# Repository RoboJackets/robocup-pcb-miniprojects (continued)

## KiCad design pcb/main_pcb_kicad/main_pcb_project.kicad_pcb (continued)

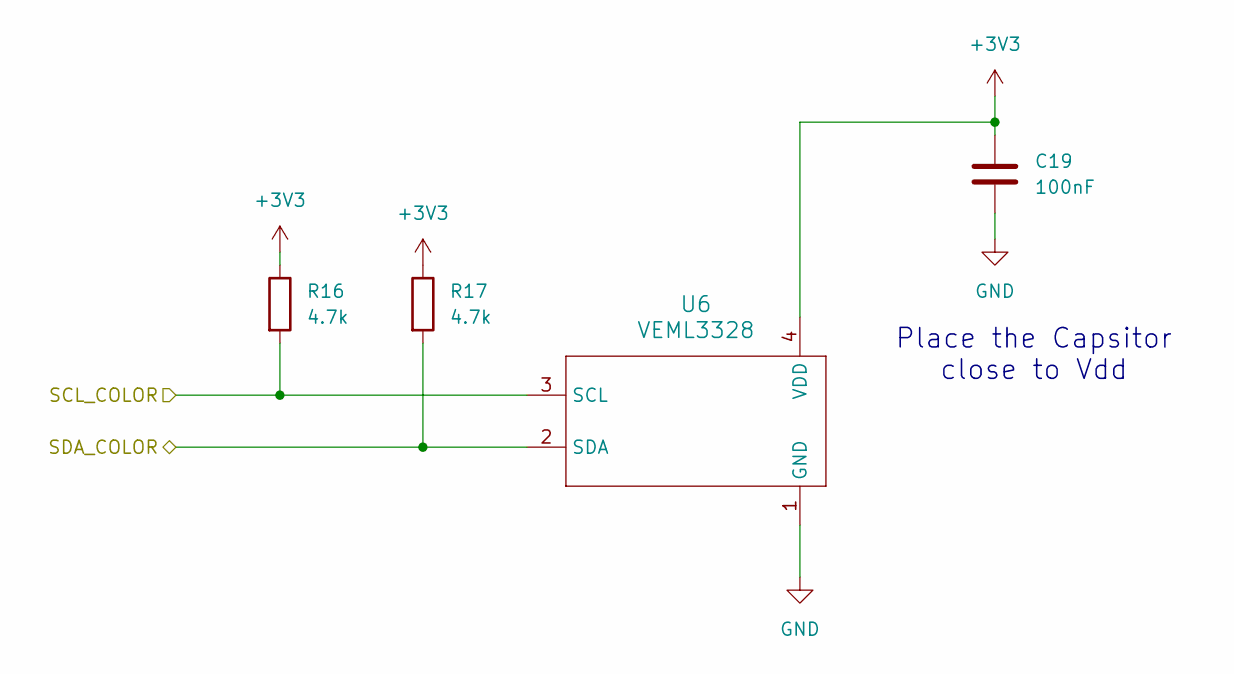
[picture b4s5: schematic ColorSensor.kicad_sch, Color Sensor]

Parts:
C19: 100nF; C_0603_1608Metric; Manufacturer P/N CC0603KRX7R9BB104
R16, R17: 4.7k; R_0402_1005Metric; Manufacturer P/N RC0402FR-074K7L
U6: VEML3328; SMD_L3328_VIS; Manufacturer P/N VEML3328

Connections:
+3V3: C19.1, R16.1, R17.1, U6.4 (VDD); also elsewhere on the board
/SCL_COLOR: R16.2, U6.3 (SCL); also elsewhere on the board
/SDA_COLOR: R17.2, U6.2 (SDA); also elsewhere on the board
GND: C19.2, U6.1 (GND); also elsewhere on the board

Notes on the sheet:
Place the Capsitor close to Vdd

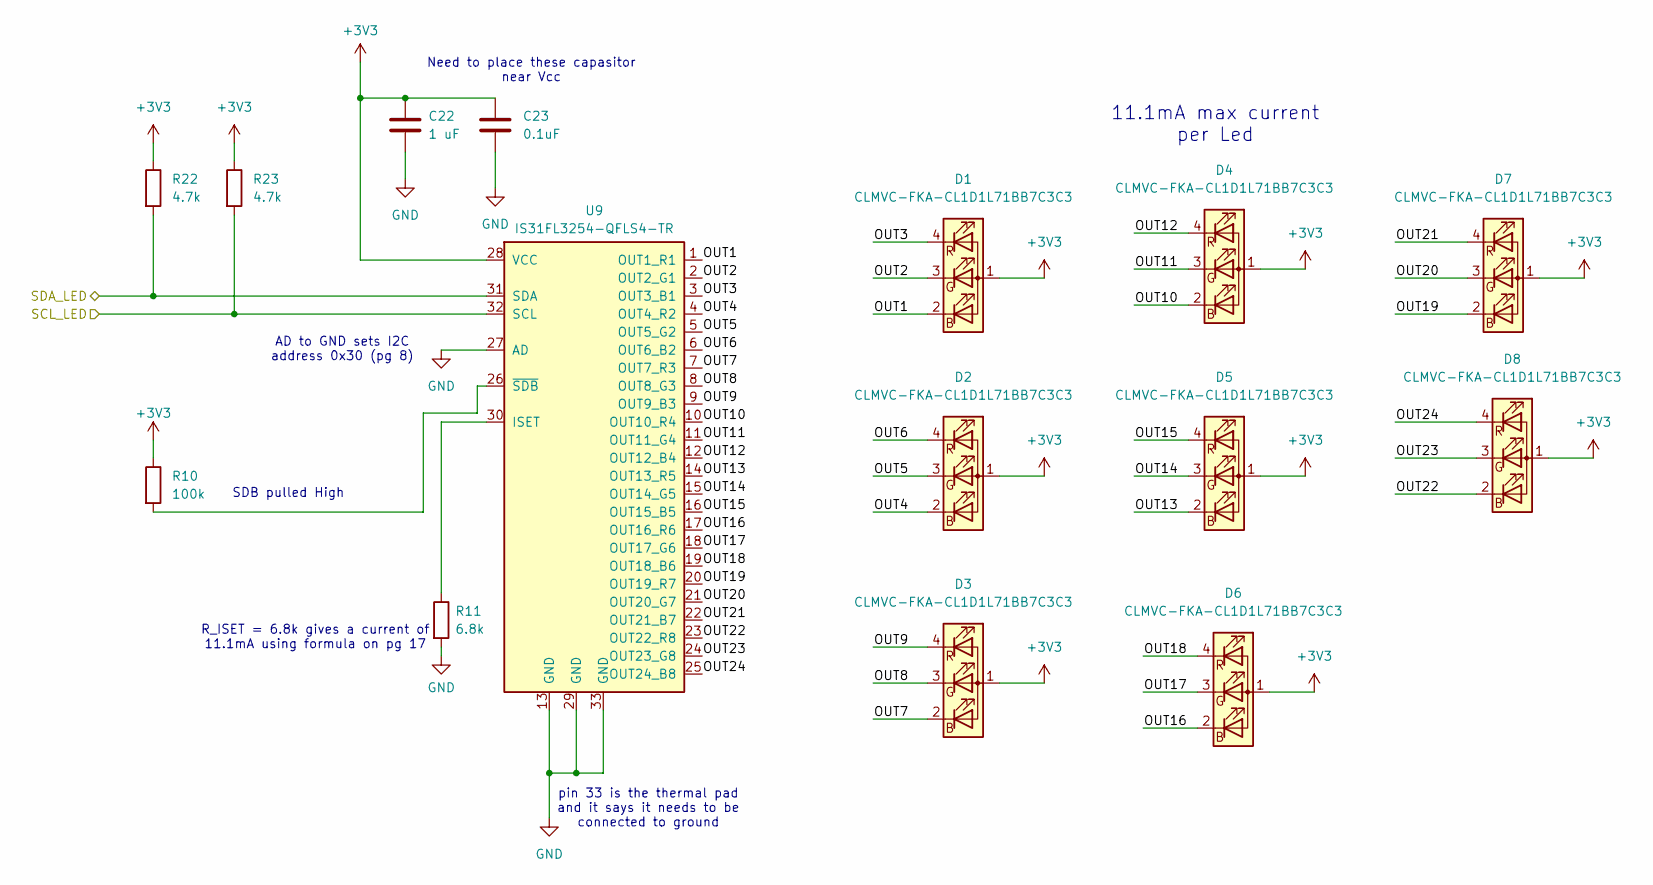
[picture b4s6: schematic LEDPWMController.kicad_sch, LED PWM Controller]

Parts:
C22: 1 uF; C_0603_1608Metric; Manufacturer P/N CC0603KRX7R7BB105
C23: 0.1uF; C_0603_1608Metric; Manufacturer P/N CL10B104KB8NNNC
D1, D2, D3, D4, D5, D6, D7, D8: CLMVC-FKA-CL1D1L71BB7C3C3; LED_Cree-PLCC4_2x2mm_CW; Manufacturer P/N CLMVC-FKA-CL1D1L71BB7C3C3
R10: 100k; R_0402_1005Metric; Manufacturer P/N RC0402FR-07100KL
R11: 6.8k; R_0402_1005Metric; Manufacturer P/N RC0402FR-076K8L
R22, R23: 4.7k; R_0402_1005Metric; Manufacturer P/N RC0402FR-074K7L
U9: IS31FL3254-QFLS4-TR; QFN-32-1EP_4x4mm_P0.4mm_EP2.65x2.65mm; Manufacturer P/N IS31FL3254-QFLS4-TR

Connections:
+3V3: C22.1, C23.1, D1.1 (A), D2.1 (A), D3.1 (A), D4.1 (A), D5.1 (A), D6.1 (A), D7.1 (A), D8.1 (A), R10.1, R22.1, R23.1, U9.28 (VCC); also elsewhere on the board
/LED PWM Controller/OUT1: D1.2 (BK), U9.1 (OUT1_R1)
/LED PWM Controller/OUT2: D1.3 (GK), U9.2 (OUT2_G1)
/LED PWM Controller/OUT3: D1.4 (RK), U9.3 (OUT3_B1)
/LED PWM Controller/OUT4: D2.2 (BK), U9.4 (OUT4_R2)
/LED PWM Controller/OUT5: D2.3 (GK), U9.5 (OUT5_G2)
/LED PWM Controller/OUT6: D2.4 (RK), U9.6 (OUT6_B2)
/LED PWM Controller/OUT7: D3.2 (BK), U9.7 (OUT7_R3)
/LED PWM Controller/OUT8: D3.3 (GK), U9.8 (OUT8_G3)
/LED PWM Controller/OUT9: D3.4 (RK), U9.9 (OUT9_B3)
/LED PWM Controller/OUT10: D4.2 (BK), U9.10 (OUT10_R4)
/LED PWM Controller/OUT11: D4.3 (GK), U9.11 (OUT11_G4)
/LED PWM Controller/OUT12: D4.4 (RK), U9.12 (OUT12_B4)
/LED PWM Controller/OUT13: D5.2 (BK), U9.14 (OUT13_R5)
/LED PWM Controller/OUT14: D5.3 (GK), U9.15 (OUT14_G5)
/LED PWM Controller/OUT15: D5.4 (RK), U9.16 (OUT15_B5)
/LED PWM Controller/OUT16: D6.2 (BK), U9.17 (OUT16_R6)
/LED PWM Controller/OUT17: D6.3 (GK), U9.18 (OUT17_G6)
/LED PWM Controller/OUT18: D6.4 (RK), U9.19 (OUT18_B6)
/LED PWM Controller/OUT19: D7.2 (BK), U9.20 (OUT19_R7)
/LED PWM Controller/OUT20: D7.3 (GK), U9.21 (OUT20_G7)
/LED PWM Controller/OUT21: D7.4 (RK), U9.22 (OUT21_B7)
/LED PWM Controller/OUT22: D8.2 (BK), U9.23 (OUT22_R8)
/LED PWM Controller/OUT23: D8.3 (GK), U9.24 (OUT23_G8)
/LED PWM Controller/OUT24: D8.4 (RK), U9.25 (OUT24_B8)
/SCL_LED: R23.2, U9.32 (SCL); also elsewhere on the board
/SDA_LED: R22.2, U9.31 (SDA); also elsewhere on the board
GND: C22.2, C23.2, R11.2, U9.13 (GND), U9.27 (AD), U9.29 (GND), U9.33 (GND); also elsewhere on the board
unnamed: R11.1, U9.30 (ISET)
unnamed: R10.2, U9.26 (~SDB)

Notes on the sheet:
11.1mA max current per Led
Need to place these capasitor near Vcc
R_ISET = 6.8k gives a current of 11.1mA using formula on pg 17
SDB pulled High
pin 33 is the thermal pad and it says it needs to be connected to ground
AD to GND sets I2C address 0x30 (pg 8)

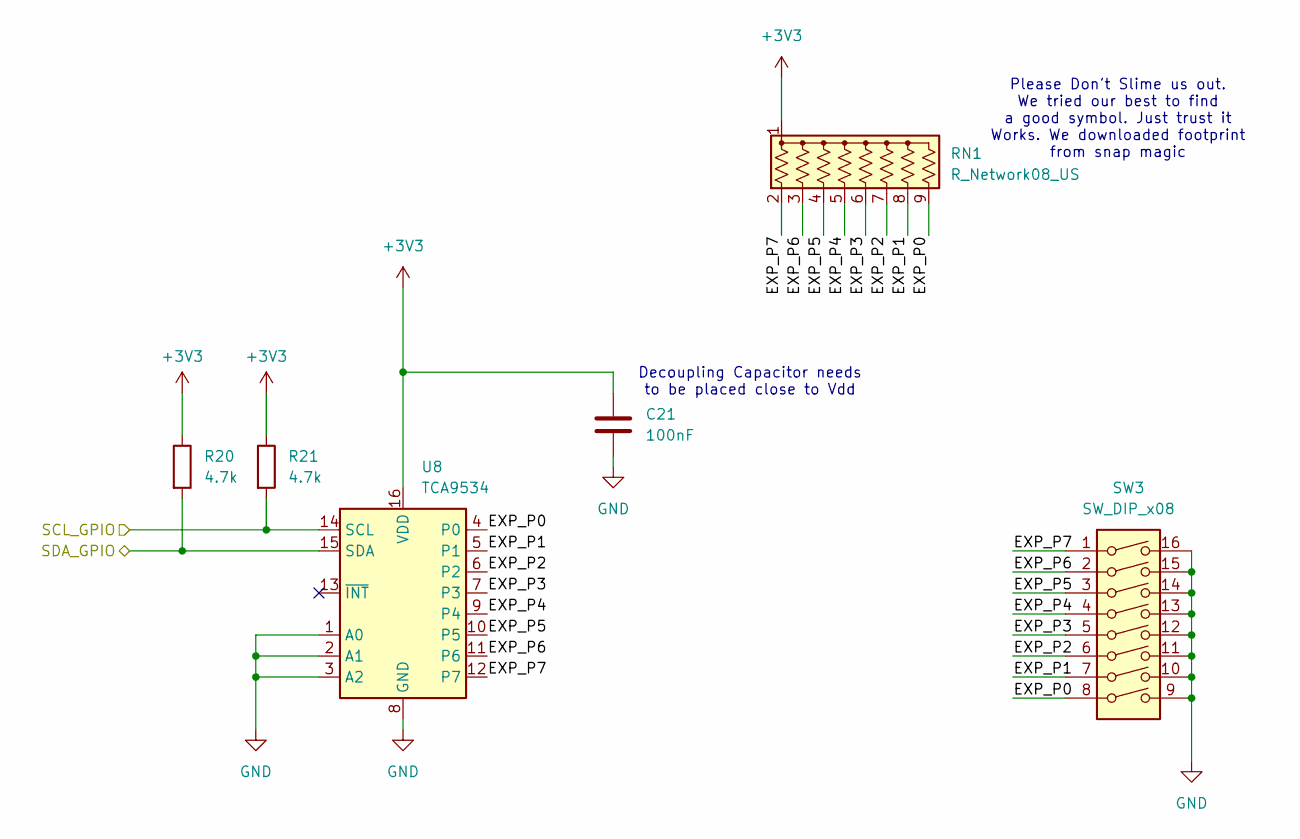
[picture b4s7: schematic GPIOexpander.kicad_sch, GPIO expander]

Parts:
C21: 100nF; C_0603_1608Metric; Manufacturer P/N CL10B104KB8NNNC
R20, R21: 4.7k; R_0402_1005Metric; Manufacturer P/N RC0402FR-074K7L
RN1: R_Network08_US; YC158_RNet08; Manufacturer P/N RC0402FR-074K7L
SW3: SW_DIP_x08; SW_DIP_SPSTx08_Slide_9.78x22.5mm_W7.62mm_P2.54mm; Manufacturer P/N DS01C-254-L-08BE
U8: TCA9534; TSSOP-16_4.4x5mm_P0.65mm; Manufacturer P/N TCA9534PWR

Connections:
+3V3: C21.1, R20.1, R21.1, RN1.1 (common), U8.16 (VDD); also elsewhere on the board
/GPIO expander/EXP_P0: RN1.9 (R8), SW3.8, U8.4 (P0)
/GPIO expander/EXP_P1: RN1.8 (R7), SW3.7, U8.5 (P1)
/GPIO expander/EXP_P2: RN1.7 (R6), SW3.6, U8.6 (P2)
/GPIO expander/EXP_P3: RN1.6 (R5), SW3.5, U8.7 (P3)
/GPIO expander/EXP_P4: RN1.5 (R4), SW3.4, U8.9 (P4)
/GPIO expander/EXP_P5: RN1.4 (R3), SW3.3, U8.10 (P5)
/GPIO expander/EXP_P6: RN1.3 (R2), SW3.2, U8.11 (P6)
/GPIO expander/EXP_P7: RN1.2 (R1), SW3.1, U8.12 (P7)
/SCL_GPIO: R21.2, U8.14 (SCL); also elsewhere on the board
/SDA_GPIO: R20.2, U8.15 (SDA); also elsewhere on the board
GND: C21.2, SW3.9, SW3.10, SW3.11, SW3.12, SW3.13, SW3.14, SW3.15, SW3.16, U8.1 (A0), U8.2 (A1), U8.3 (A2), U8.8 (GND); also elsewhere on the board

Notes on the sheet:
Decoupling Capacitor needs to be placed close to Vdd
Please Don't Slime us out. We tried our best to find a good symbol. Just trust it Works. We downloaded footprint from snap magic

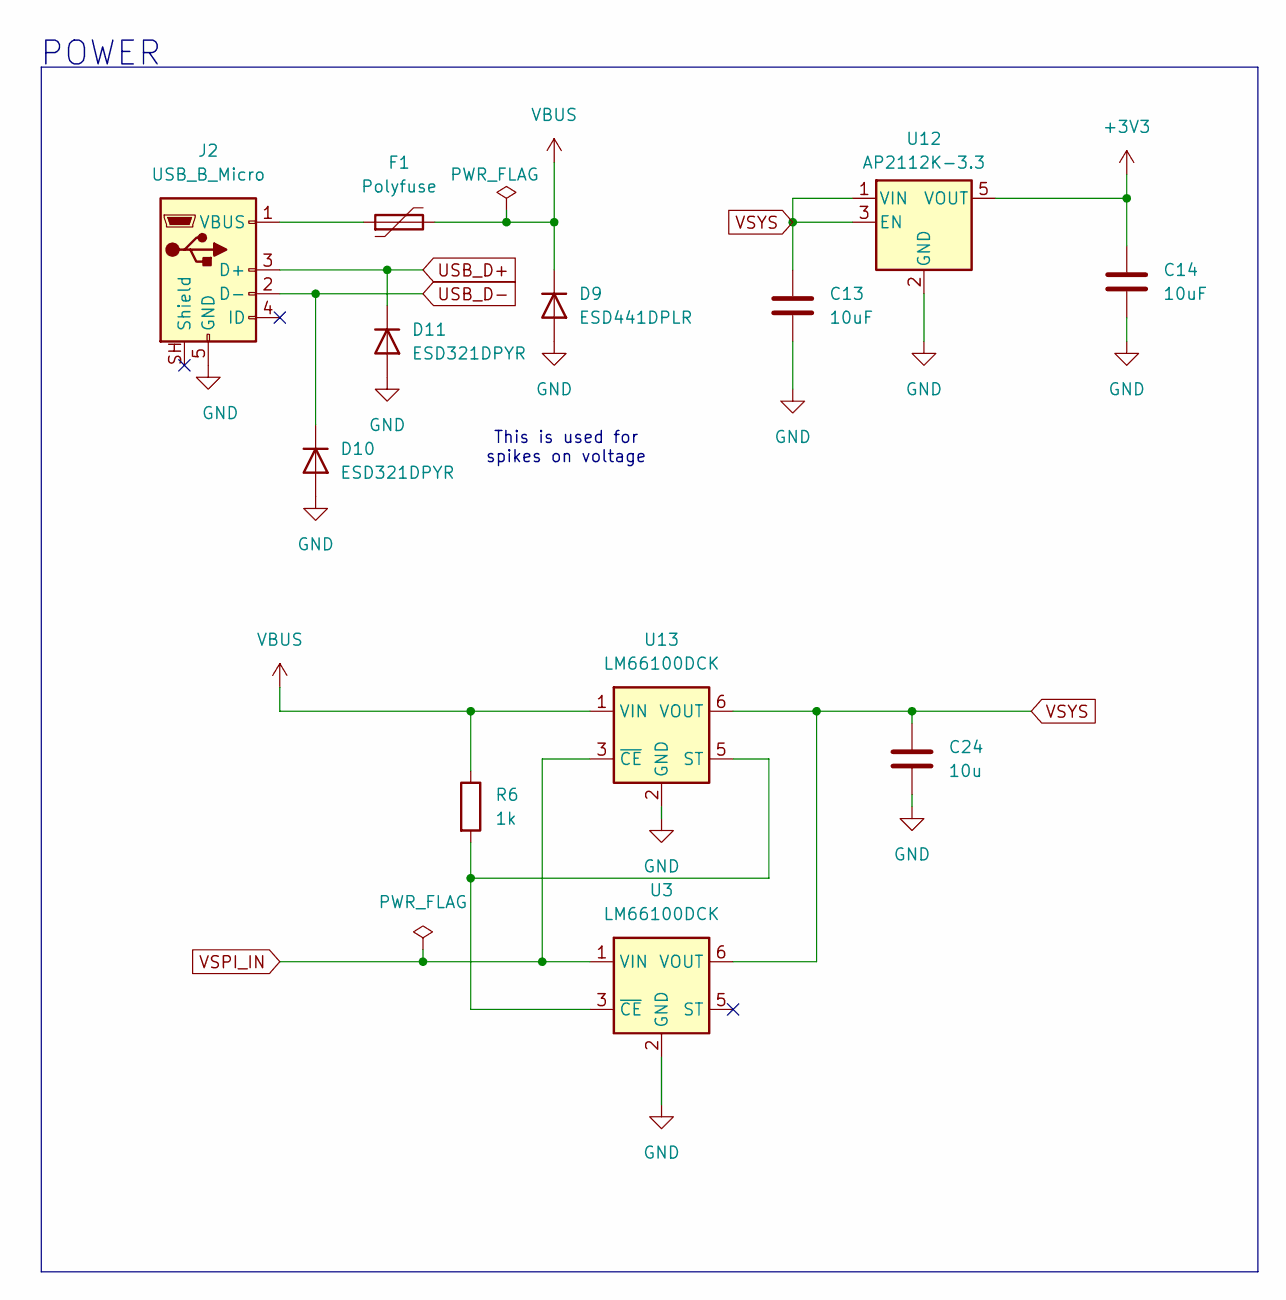
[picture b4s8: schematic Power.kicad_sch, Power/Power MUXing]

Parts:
C13, C14: 10uF; C_0402_1005Metric; Manufacturer P/N C0805C106M4PACTU
C24: 10u; C_0402_1005Metric; Manufacturer P/N C0805C106M4PACTU
D9: ESD441DPLR; D_0201_0603Metric; Manufacturer P/N ESD441DPLR
D10, D11: ESD321DPYR; D_0402_1005Metric; Manufacturer P/N ESD351DPYR
F1: Polyfuse; Fuse_1206_3216Metric; Manufacturer P/N 0ZCJ0050FF2G
J2: USB_B_Micro; USB_Micro-B_Amphenol_10118194_Horizontal; Manufacturer P/N 10118194-0001LF
R6: 1k; R_0402_1005Metric; Manufacturer P/N RC0402FR-071KL
U3, U13: LM66100DCK; SOT-363_SC-70-6; Manufacturer P/N LM66100DCKR
U12: AP2112K-3.3; SOT-23-5; Manufacturer P/N AP2112K-3.3TRG1

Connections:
+3V3: C14.1, U12.5 (VOUT); also elsewhere on the board
GND: C13.2, C14.2, C24.2, D9.2 (A), D10.2 (A), D11.2 (A), J2.5 (GND), U3.2 (GND), U12.2 (GND), U13.2 (GND); also elsewhere on the board
unnamed: F1.1, J2.1 (VBUS)
unnamed: R6.2, U3.3 (~CE), U13.5 (ST)
USB_D+: D11.1 (K), J2.3 (D+); also elsewhere on the board
USB_D-: D10.1 (K), J2.2 (D-); also elsewhere on the board
VBUS: D9.1 (K), F1.2, R6.1, U13.1 (VIN); also elsewhere on the board
VSPI_IN: U3.1 (VIN), U13.3 (~CE); also elsewhere on the board
VSYS: C13.1, C24.1, U3.6 (VOUT), U12.1 (VIN), U12.3 (EN), U13.6 (VOUT); also elsewhere on the board

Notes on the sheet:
POWER
This is used for spikes on voltage

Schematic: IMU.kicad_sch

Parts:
C15: 0.1uF; C_0603_1608Metric; Manufacturer P/N CL10B104KB8NNNC
C16: 2.2uF; C_0603_1608Metric; Manufacturer P/N CL10B225KP8NNNC
C17: 10nF; C_0603_1608Metric; Manufacturer P/N CL10B103KB8NNNC
R12, R13: 4.7k; R_0402_1005Metric; Manufacturer P/N RC0402FR-074K7L
U4: ICM-42605; LGA14_2P5X3X0P91_IVS-L; Manufacturer P/N ICM-42605

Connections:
+3V3: C15.1, C16.1, C17.1, R12.1, R13.1, U4.5 (VDDIO), U4.8 (VDD), U4.12 (AP_CS); also elsewhere on the board
/SCL_IMU: R12.2, U4.13 (AP_SCL/AP_SCLK); also elsewhere on the board
/SDA_IMU: R13.2, U4.14 (AP_SDA/AP_SDIO/AP_SDI); also elsewhere on the board
GND: C15.2, C16.2, C17.2, U4.1 (AP_SDO/AP_AD0), U4.6 (GND), U4.7 (RESV), U4.9 (INT2/FSYNC); also elsewhere on the board

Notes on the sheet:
These are pull up resistors
Please don't slime us out. We tried our best to make another design but things happened and we were unable Sorry :(
These capacitors need to be placed close to Vdd
Place capacitor close to VDDIO

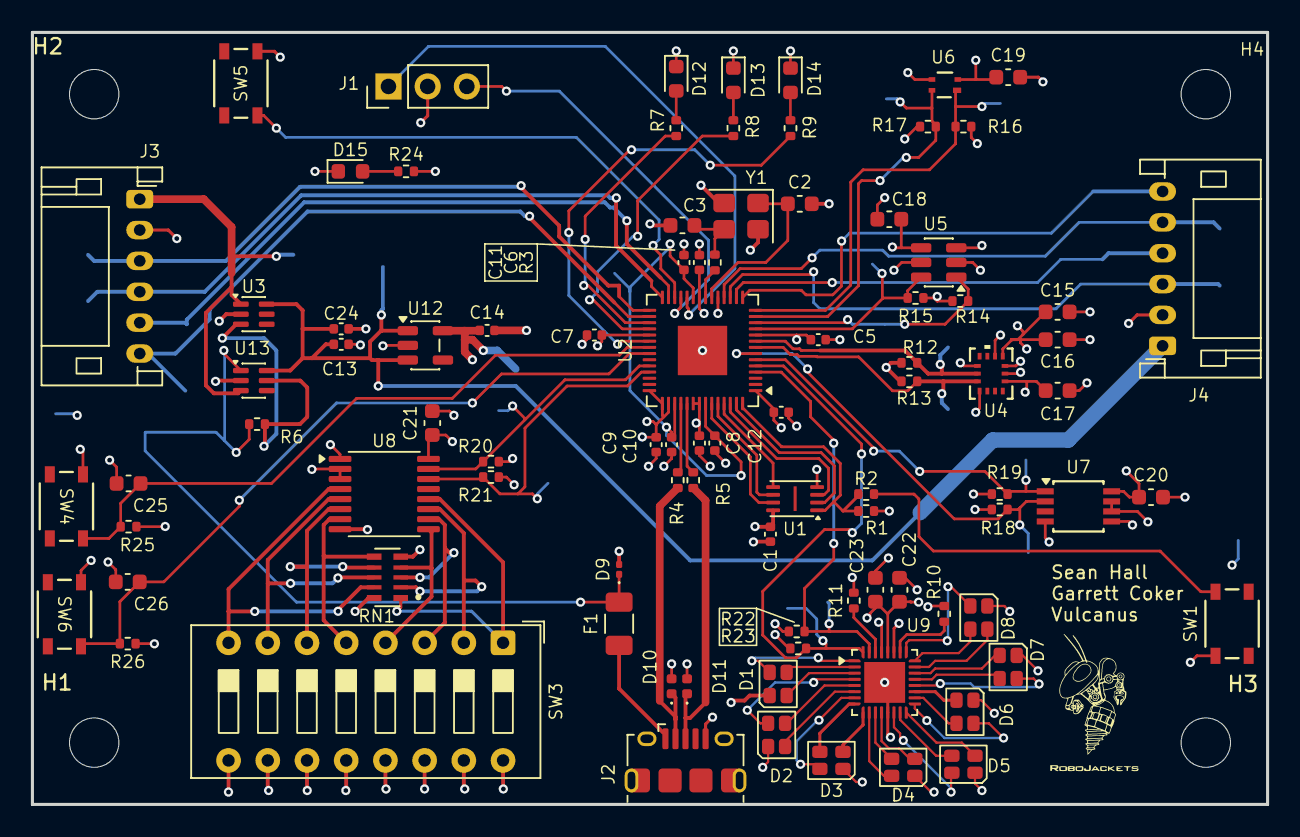
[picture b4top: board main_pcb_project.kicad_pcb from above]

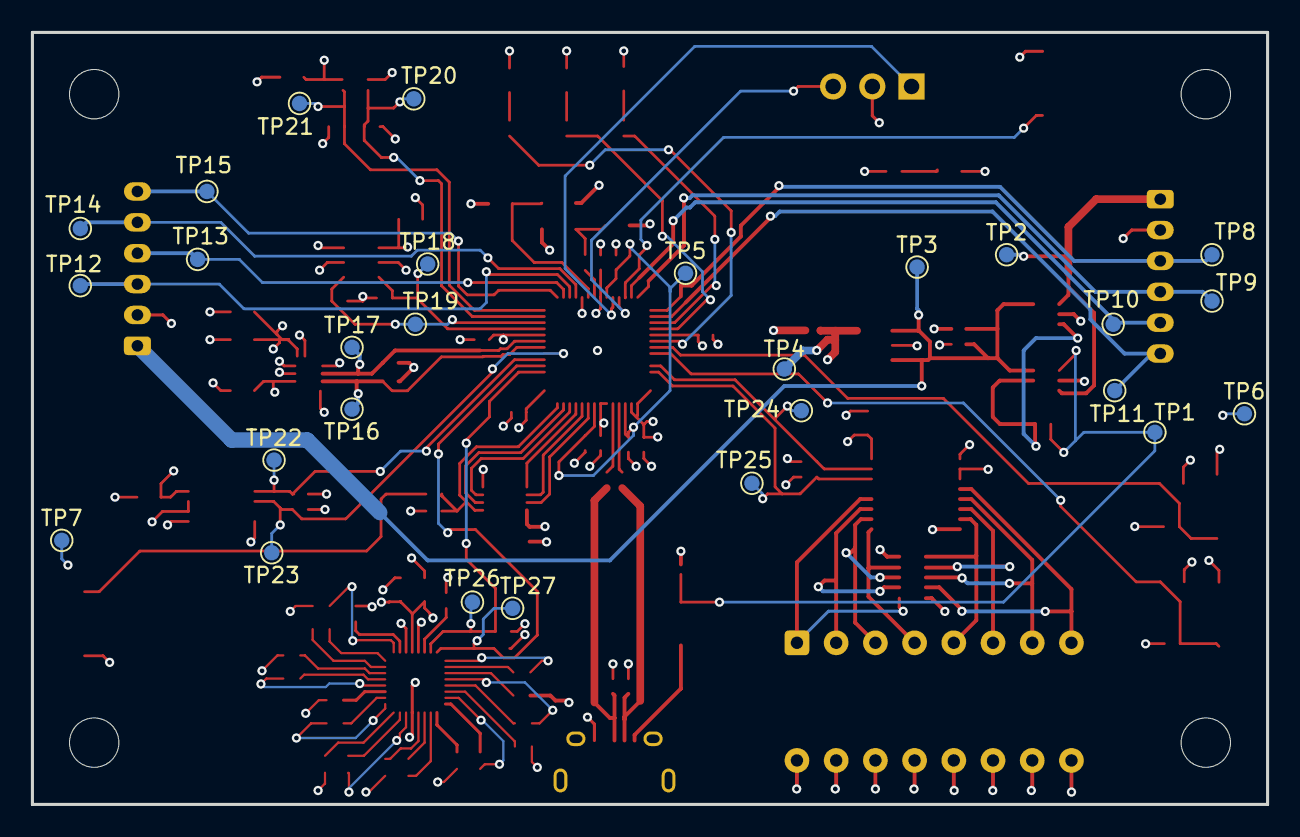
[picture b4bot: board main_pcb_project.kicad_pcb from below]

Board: 4 copper layers, 80.0 x 50.0 mm, 121 parts (27 on the bottom side), 88 nets.

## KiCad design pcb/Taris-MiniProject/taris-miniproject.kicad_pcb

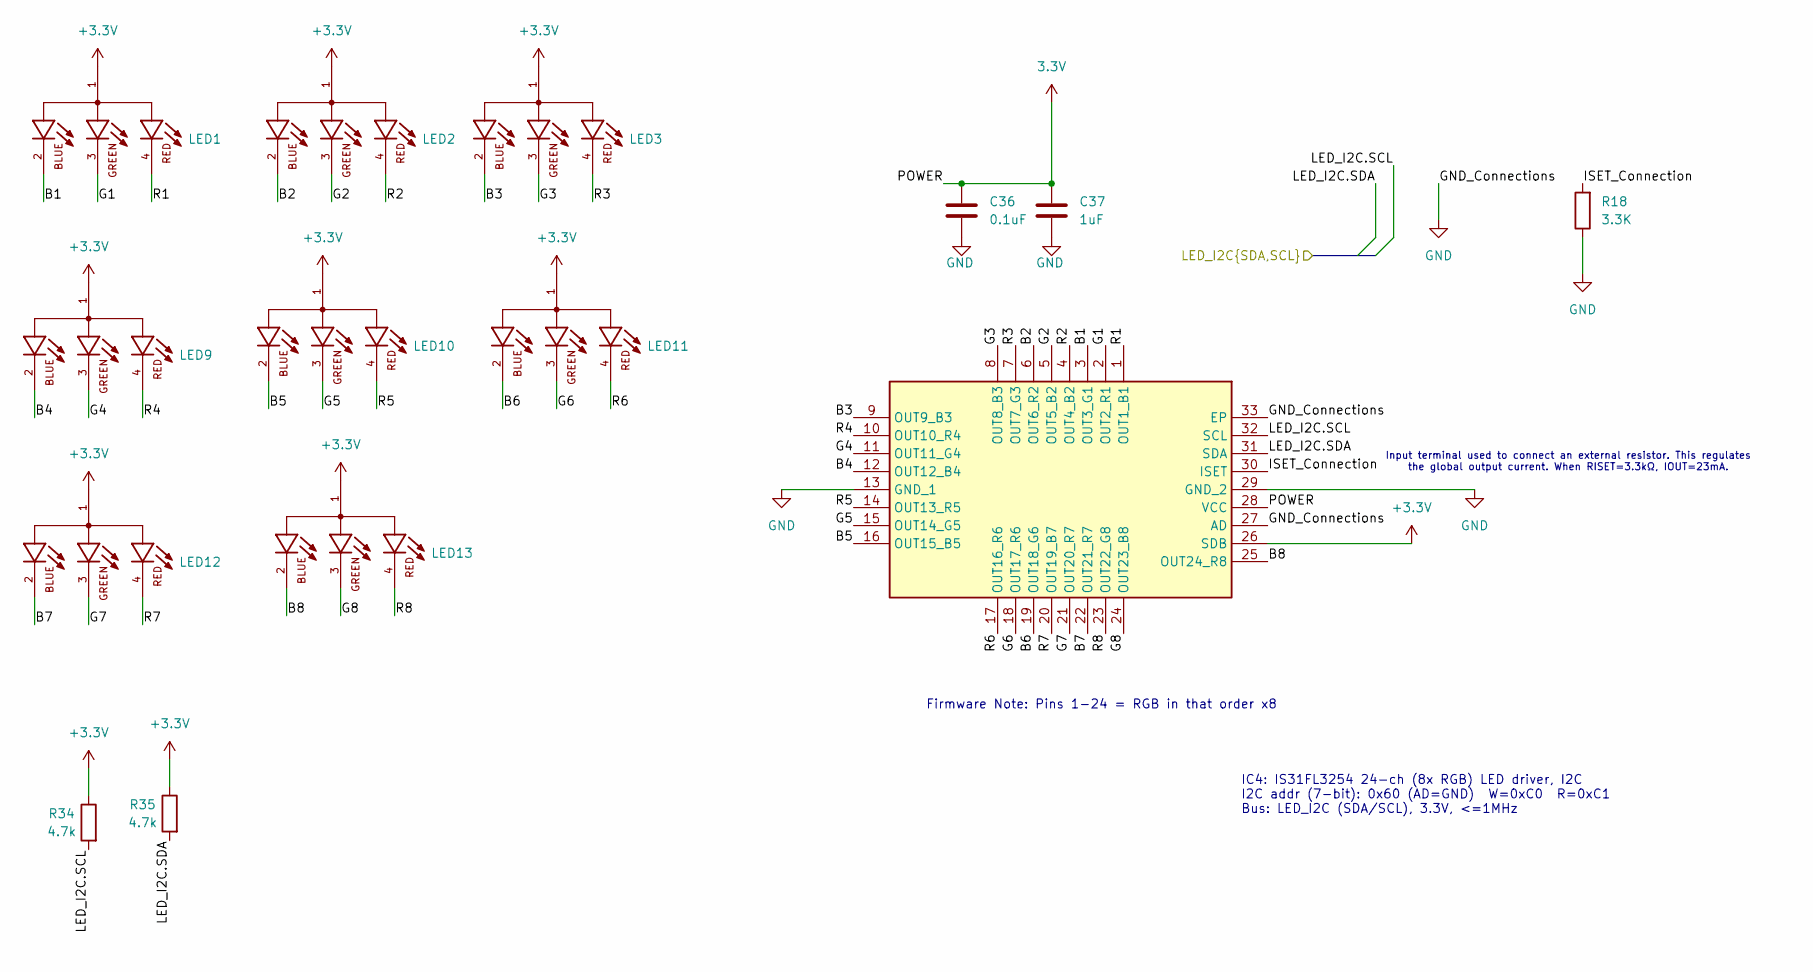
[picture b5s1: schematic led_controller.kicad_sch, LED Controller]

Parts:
C36: 0.1uF; C_0603_1608Metric; Manufacturer P/N CC0603KRX5R8BB104
C37: 1uF; C_0603_1608Metric; Manufacturer P/N GMC04X7R105K10NT
IC4: IS31FL3254-QFLS4-TR; QFN40P400X400X80-33N-D; Manufacturer_Part_Number IS31FL3254-QFLS4-TR
LED1, LED2, LED3, LED9, LED10, LED11, LED12, LED13: CLMVC-FKA-CL1D1L71BB7C3C3; LED_CLMVC-FKA-CL1D1L71BB7C3C3; PARTREV 14; DigiKey_Part_Number CLMVC-FKA-CL1D1L71BB7C3C3CT-ND
R18: 3.3K; R_0603_1608Metric; Manufacturer P/N RC0603FR-073K3L
R34, R35: 4.7k; R_0402_1005Metric; Manufacturer P/N RC0402FR-134K7L

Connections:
3.3V: C36.1, C37.1, IC4.28 (VCC); also elsewhere on the board
+3.3V: IC4.26 (SDB), LED1.1, LED2.1, LED3.1, LED9.1, LED10.1, LED11.1, LED12.1, LED13.1, R34.1, R35.1; also elsewhere on the board
/LED Controller/B1: IC4.3 (OUT3_G1), LED1.2
/LED Controller/B2: IC4.6 (OUT6_R2), LED2.2
/LED Controller/B3: IC4.9 (OUT9_B3), LED3.2
/LED Controller/B4: IC4.12 (OUT12_B4), LED9.2
/LED Controller/B5: IC4.16 (OUT15_B5), LED10.2
/LED Controller/B6: IC4.19 (OUT18_G6), LED11.2
/LED Controller/B7: IC4.22 (OUT21_R7), LED12.2
/LED Controller/B8: IC4.25 (OUT24_R8), LED13.2
/LED Controller/G1: IC4.2 (OUT2_R1), LED1.3
/LED Controller/G2: IC4.5 (OUT5_B2), LED2.3
/LED Controller/G3: IC4.8 (OUT8_B3), LED3.3
/LED Controller/G4: IC4.11 (OUT11_G4), LED9.3
/LED Controller/G5: IC4.15 (OUT14_G5), LED10.3
/LED Controller/G6: IC4.18 (OUT17_R6), LED11.3
/LED Controller/G7: IC4.21 (OUT20_R7), LED12.3
/LED Controller/G8: IC4.24 (OUT23_B8), LED13.3
/LED Controller/ISET_Connection: IC4.30 (ISET), R18.2
/LED Controller/R1: IC4.1 (OUT1_B1), LED1.4
/LED Controller/R2: IC4.4 (OUT4_B2), LED2.4
/LED Controller/R3: IC4.7 (OUT7_G3), LED3.4
/LED Controller/R4: IC4.10 (OUT10_R4), LED9.4
/LED Controller/R5: IC4.14 (OUT13_R5), LED10.4
/LED Controller/R6: IC4.17 (OUT16_R6), LED11.4
/LED Controller/R7: IC4.20 (OUT19_B7), LED12.4
/LED Controller/R8: IC4.23 (OUT22_G8), LED13.4
/LED_I2C.SCL: IC4.32 (SCL), R34.2; also elsewhere on the board
/LED_I2C.SDA: IC4.31 (SDA), R35.2; also elsewhere on the board
GND: C36.2, C37.2, IC4.13 (GND_1), IC4.27 (AD), IC4.29 (GND_2), IC4.33 (EP), R18.1; also elsewhere on the board

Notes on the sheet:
Firmware Note: Pins 1-24 = RGB in that order x8
IC4: IS31FL3254 24-ch (8x RGB) LED driver, I2C I2C addr (7-bit): 0x60 (AD=GND) W=0xC0 R=0xC1 Bus: LED_I2C (SDA/SCL), 3.3V, <=1MHz
Input terminal used to connect an external resistor. This regulates the global output current. When RISET=3.3kΩ, IOUT=23mA.

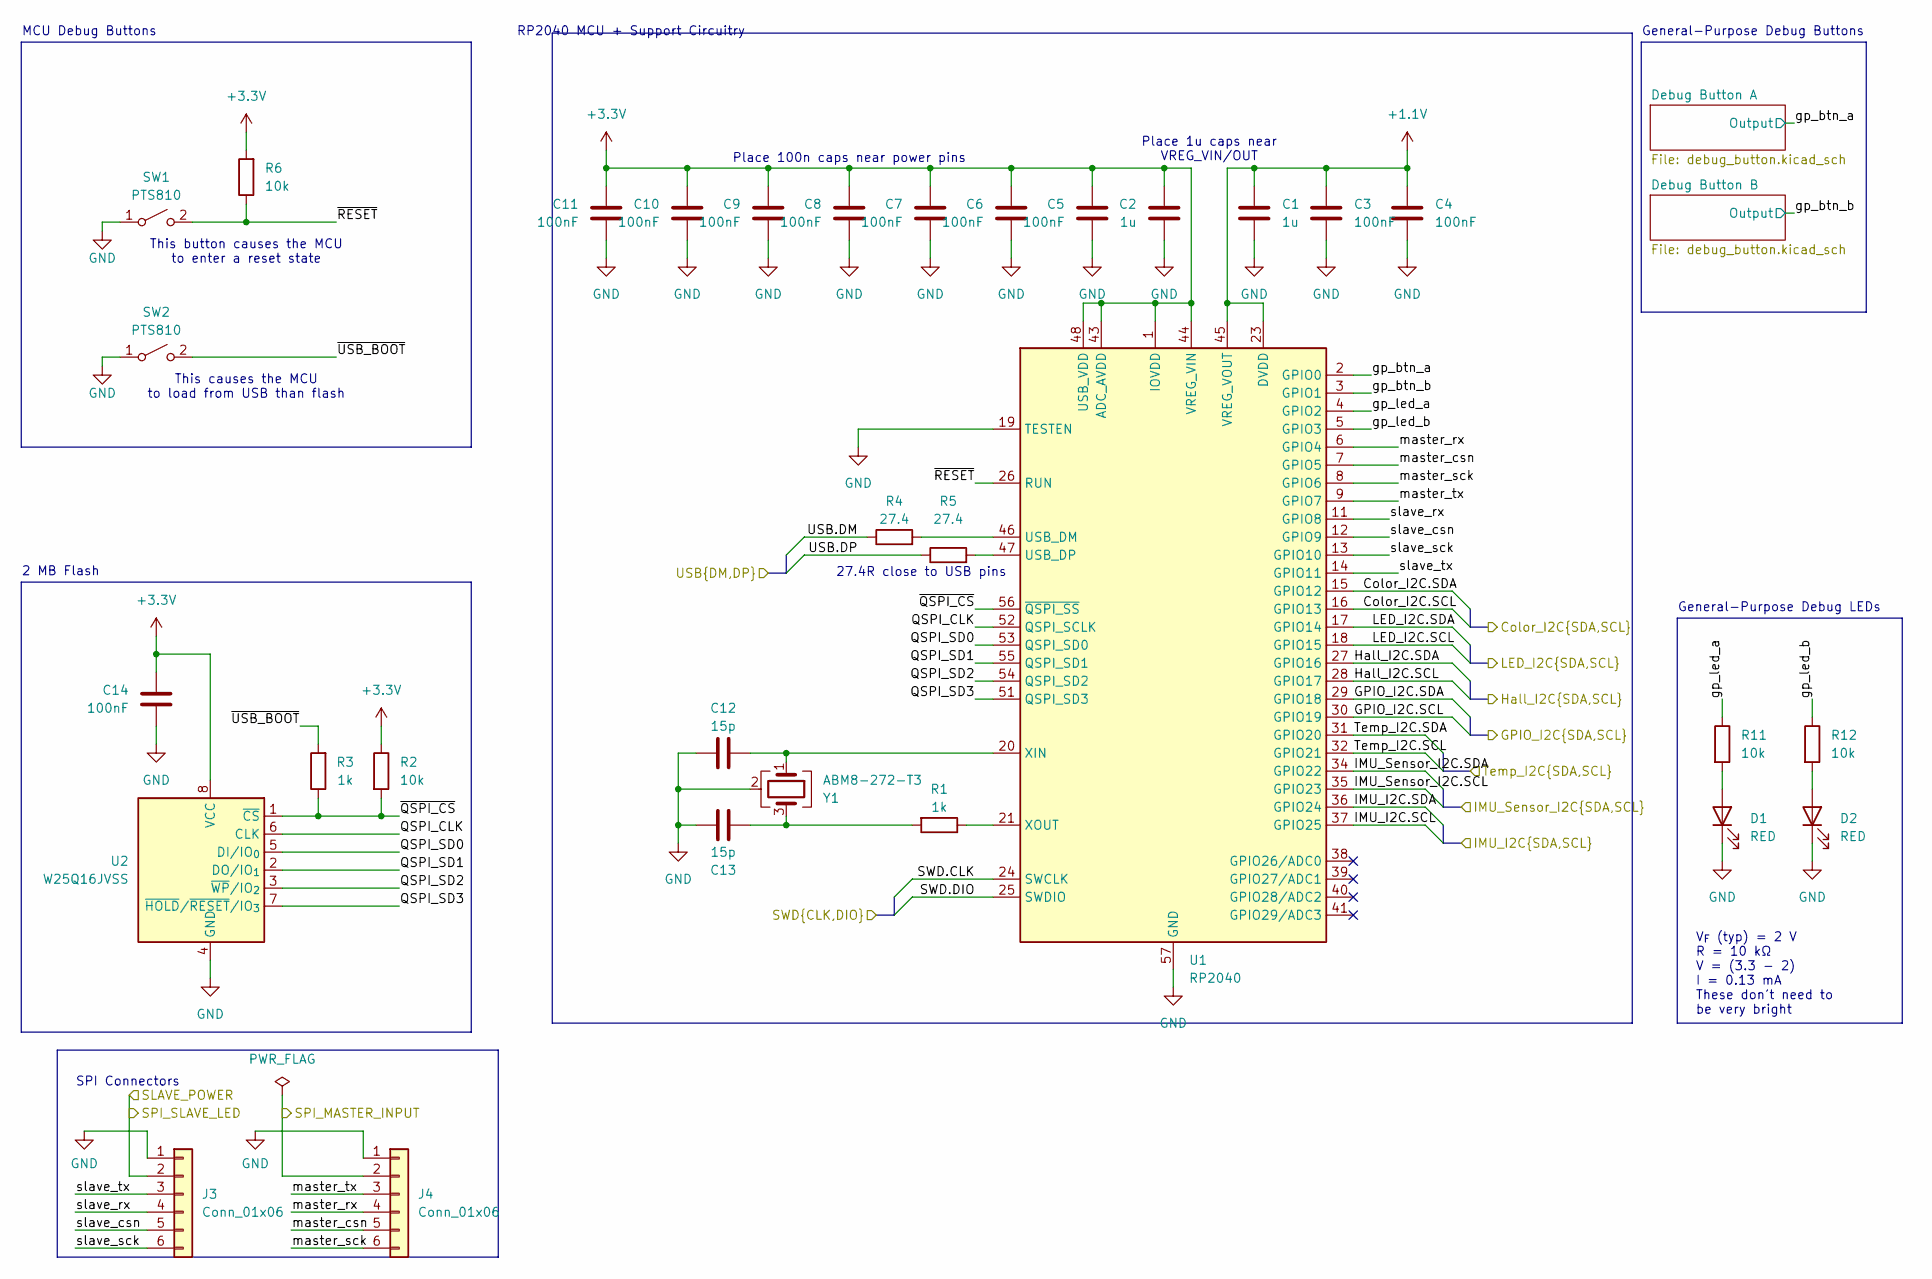
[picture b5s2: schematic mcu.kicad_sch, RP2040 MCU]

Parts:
C1, C2: 1u; C_0402_1005Metric; Manufacturer P/N GRM155Z71A105KE01J
C3, C4, C5, C6, C7, C8, C9, C10, C11, C14: 100nF; C_0402_1005Metric; Manufacturer P/N CC0603KRX5R8BB104
C12, C13: 15p; C_0402_1005Metric; Manufacturer P/N GRM1555C1H150JA01D
D1, D2: RED; LED_0603_1608Metric; Manufacturer P/N LTST-C190KRKT
J3, J4: Conn_01x06; JST_PH_S6B-PH-K_1x06_P2.00mm_Horizontal; Manufacturer P/N S6B-PH-K-S
R1, R3: 1k; R_0402_1005Metric; Manufacturer P/N RC0402FR-071KL
R2, R6, R11, R12: 10k; R_0402_1005Metric; Manufacturer P/N RC0402FR-0710KL
R4, R5: 27.4; R_0402_1005Metric; Manufacturer P/N RC0402FR-0727R4L
SW1, SW2: PTS810; SW_SPST_PTS810; Manufacturer P/N PTS810SJK250SMTR LFS
U1: RP2040; QFN-56-1EP_7x7mm_P0.4mm_EP3.2x3.2mm; Manufacturer P/N SC0914(13)
U2: W25Q16JVSS; SOIC-8_5.3x5.3mm_P1.27mm; Manufacturer P/N W25Q16JVSSIQ
Y1: ABM8-272-T3; Crystal_SMD_Abracon_ABM8AIG-4Pin_3.2x2.5mm; Manufacturer P/N ABM8-272-T3

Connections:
+1.1V: C1.1, C3.1, C4.1, U1.23 (DVDD), U1.45 (VREG_VOUT), U1.50 (DVDD)
+3.3V: C2.1, C5.1, C6.1, C7.1, C8.1, C9.1, C10.1, C11.1, C14.1, R2.1, R6.2, U1.1 (IOVDD), U1.10 (IOVDD), U1.22 (IOVDD), U1.33 (IOVDD), U1.42 (IOVDD), U1.43 (ADC_AVDD), U1.44 (VREG_VIN), U1.48 (USB_VDD), U1.49 (IOVDD), U2.8 (VCC); also elsewhere on the board
/Color_I2C.SCL: U1.16 (GPIO13); also elsewhere on the board
/Color_I2C.SDA: U1.15 (GPIO12); also elsewhere on the board
/GPIO_I2C.SCL: U1.30 (GPIO19); also elsewhere on the board
/GPIO_I2C.SDA: U1.29 (GPIO18); also elsewhere on the board
/Hall_I2C.SCL: U1.28 (GPIO17); also elsewhere on the board
/Hall_I2C.SDA: U1.27 (GPIO16); also elsewhere on the board
/IMU_I2C.SCL: U1.37 (GPIO25); also elsewhere on the board
/IMU_I2C.SDA: U1.36 (GPIO24); also elsewhere on the board
/IMU_Sensor_I2C.SCL: U1.35 (GPIO23); also elsewhere on the board
/IMU_Sensor_I2C.SDA: U1.34 (GPIO22); also elsewhere on the board
/LED_I2C.SCL: U1.18 (GPIO15); also elsewhere on the board
/LED_I2C.SDA: U1.17 (GPIO14); also elsewhere on the board
/MCU/QSPI_CLK: U1.52 (QSPI_SCLK), U2.6 (CLK)
/MCU/QSPI_SD0: U1.53 (QSPI_SD0), U2.5 (DI/IO_{0})
/MCU/QSPI_SD1: U1.55 (QSPI_SD1), U2.2 (DO/IO_{1})
/MCU/QSPI_SD2: U1.54 (QSPI_SD2), U2.3 (~WP/IO_{2})
/MCU/QSPI_SD3: U1.51 (QSPI_SD3), U2.7 (~HOLD/~RESET/IO_{3})
/MCU/gp_btn_a: U1.2 (GPIO0); also elsewhere on the board
/MCU/gp_btn_b: U1.3 (GPIO1); also elsewhere on the board
/MCU/gp_led_a: R11.1, U1.4 (GPIO2)
/MCU/gp_led_b: R12.1, U1.5 (GPIO3)
/MCU/master_csn: J4.5, U1.7 (GPIO5)
/MCU/master_rx: J4.4, U1.6 (GPIO4)
/MCU/master_sck: J4.6, U1.8 (GPIO6)
/MCU/master_tx: J4.3, U1.9 (GPIO7)
/MCU/slave_csn: J3.5, U1.12 (GPIO9)
/MCU/slave_rx: J3.4, U1.11 (GPIO8)
/MCU/slave_sck: J3.6, U1.13 (GPIO10)
/MCU/slave_tx: J3.3, U1.14 (GPIO11)
/MCU/~QSPI_CS: R2.2, R3.1, U1.56 (~QSPI_SS), U2.1 (~CS)
/MCU/~RESET: R6.1, SW1.2 (B), U1.26 (RUN)
/MCU/~USB_BOOT: R3.2, SW2.2 (B)
/SLAVE_POWER: J3.2; also elsewhere on the board
/SPI_MASTER_INPUT: J4.2; also elsewhere on the board
/SWD.CLK: U1.24 (SWCLK); also elsewhere on the board
/SWD.DIO: U1.25 (SWDIO); also elsewhere on the board
/Temp_I2C.SCL: U1.32 (GPIO21); also elsewhere on the board
/Temp_I2C.SDA: U1.31 (GPIO20); also elsewhere on the board
/USB.DM: R4.1; also elsewhere on the board
/USB.DP: R5.1; also elsewhere on the board
GND: C1.2, C2.2, C3.2, C4.2, C5.2, C6.2, C7.2, C8.2, C9.2, C10.2, C11.2, C12.1, C13.1, C14.2, D1.1 (K), D2.1 (K), J3.1, J4.1, SW1.1 (A), SW2.1 (A), U1.19 (TESTEN), U1.57 (GND), U2.4 (GND), Y1.2 (G), Y1.4 (G); also elsewhere on the board
unnamed: C13.2, R1.2, Y1.3
unnamed: D1.2 (A), R11.2
unnamed: D2.2 (A), R12.2
unnamed: R4.2, U1.46 (USB_DM)
unnamed: R5.2, U1.47 (USB_DP)
unnamed: C12.2, U1.20 (XIN), Y1.1
unnamed: R1.1, U1.21 (XOUT)

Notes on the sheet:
V_{F} (typ) = 2 V R = 10 kΩ V = (3.3 - 2) I = 0.13 mA These don't need to be very bright
General-Purpose Debug Buttons
This causes the MCU to load from USB than flash
2 MB Flash
RP2040 MCU + Support Circuitry
This button causes the MCU to enter a reset state
MCU Debug Buttons
Place 100n caps near power pins
SPI Connectors
General-Purpose Debug LEDs
Place 1u caps near VREG_VIN/OUT
27.4R close to USB pins

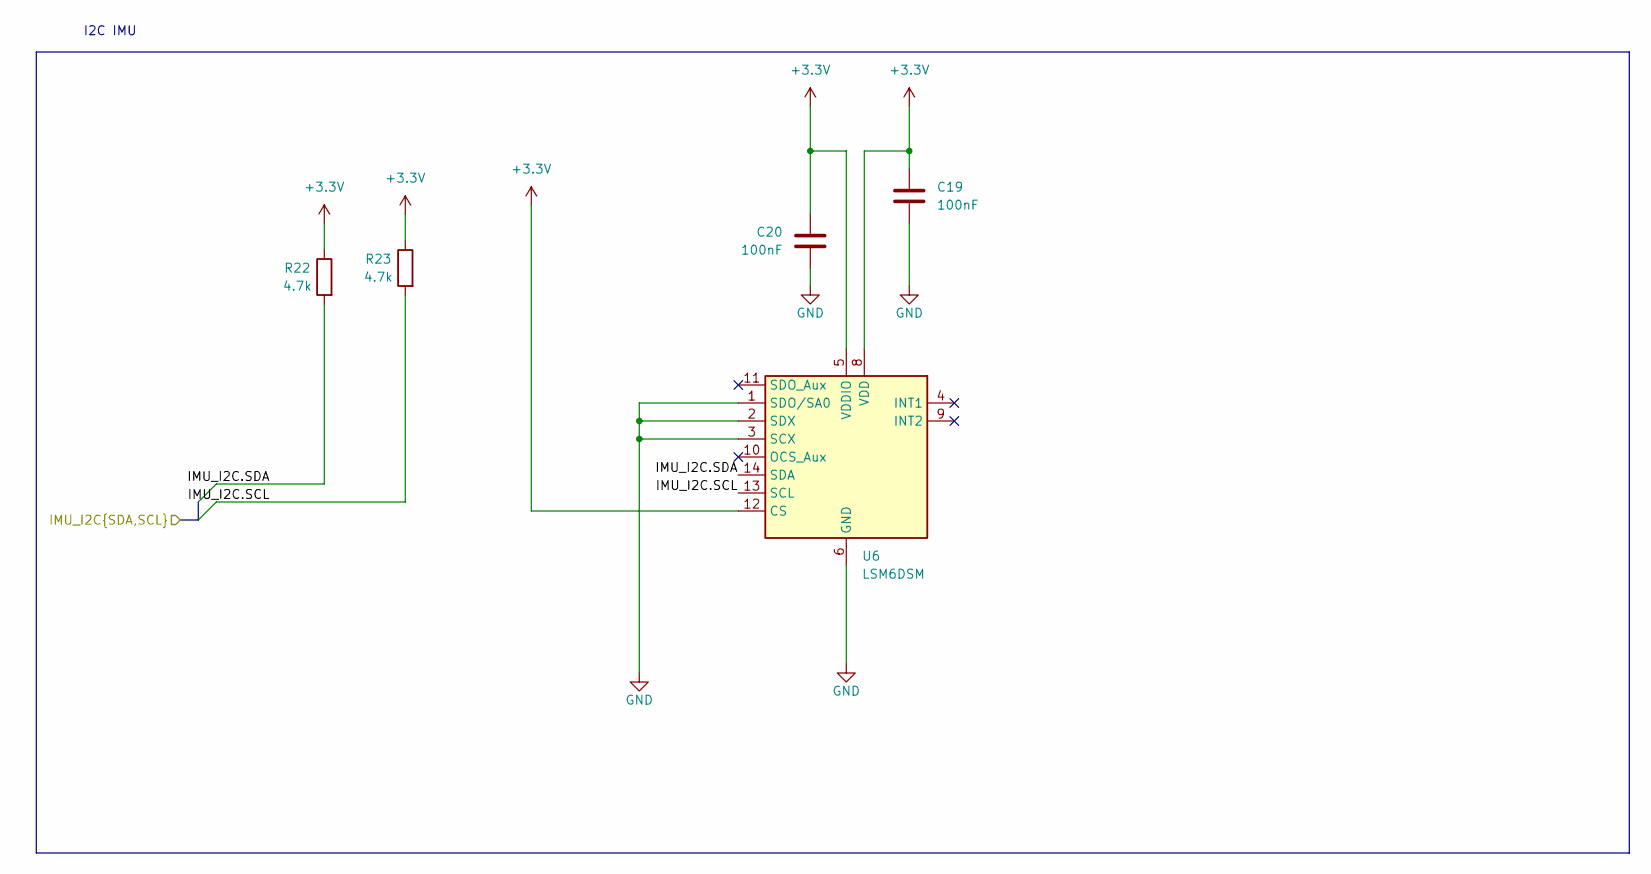
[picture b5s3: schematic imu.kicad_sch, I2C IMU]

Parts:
C19, C20: 100nF; C_0402_1005Metric; Manufacturer P/N CC0603KRX5R8BB104
R22, R23: 4.7k; R_0402_1005Metric; Manufacturer P/N RC0402FR-134K7L
U6: LSM6DSM; LGA-14_3x2.5mm_P0.5mm_LayoutBorder3x4y; Manufacturer P/N LSM6DSMTR

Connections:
+3.3V: C19.1, C20.1, R22.1, R23.1, U6.5 (VDDIO), U6.8 (VDD), U6.12 (CS); also elsewhere on the board
/IMU_I2C.SCL: R23.2, U6.13 (SCL); also elsewhere on the board
/IMU_I2C.SDA: R22.2, U6.14 (SDA); also elsewhere on the board
GND: C19.2, C20.2, U6.1 (SDO/SA0), U6.2 (SDX), U6.3 (SCX), U6.6 (GND), U6.7 (GND); also elsewhere on the board

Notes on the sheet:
I2C IMU
